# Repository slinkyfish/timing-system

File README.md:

# timing-system
Components for a micromouse and line follower contest timing system.

Initial development will be related to a drag race timer. 

The contest is described here: https://ukmars.org/contests/drag-race/

And the rules are here: https://ukmars.org/contests/contest-rules/drag-race/

The `legacy` folder contains design files for the existing equipment used in UK contests at Birmingham City University and originally designed by Tony Wilcox.

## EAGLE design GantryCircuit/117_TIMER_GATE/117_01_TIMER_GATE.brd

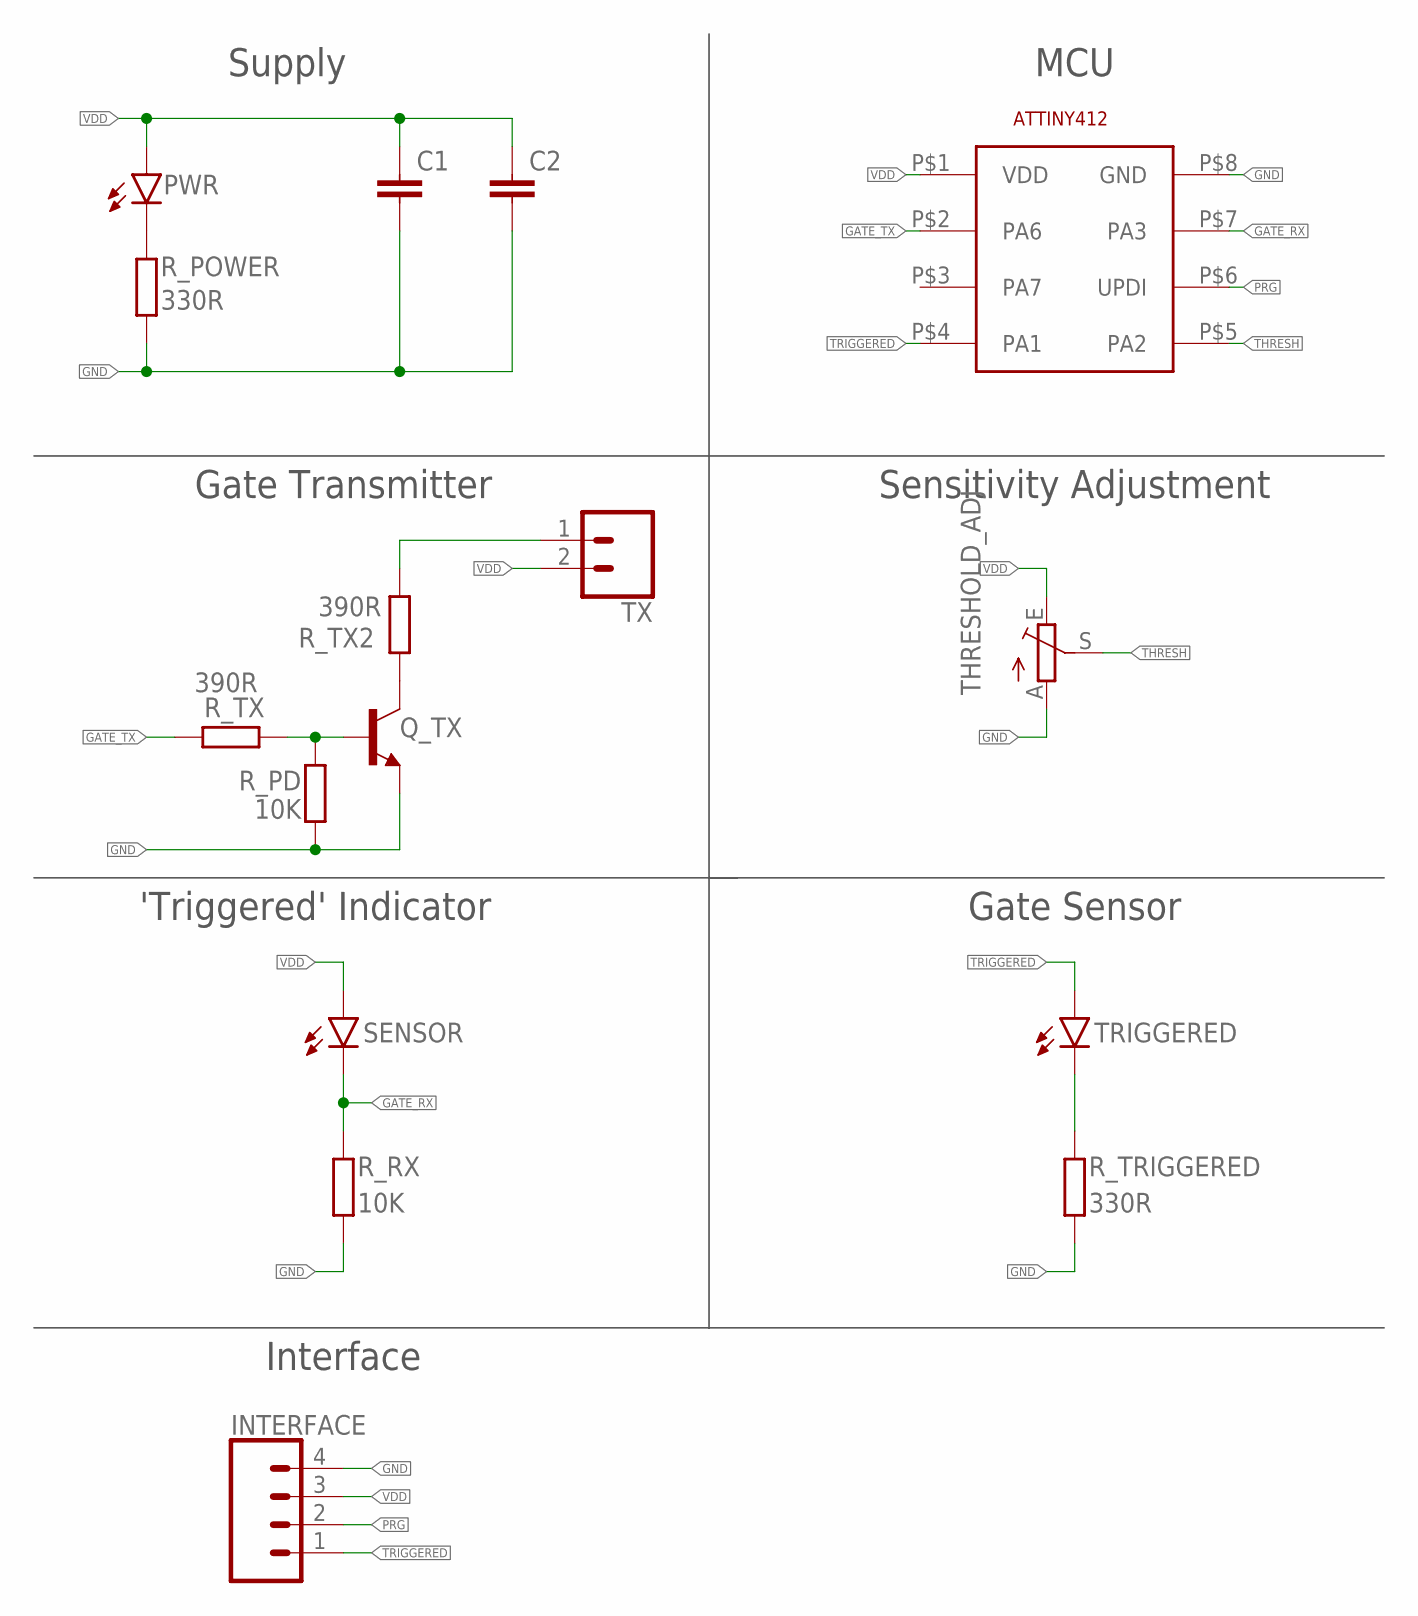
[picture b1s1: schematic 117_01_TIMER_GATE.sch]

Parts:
C1, C2: C-EUC0805K; C0805K
INTERFACE: CONN_04LONGPADS; 1X04_LONGPADS
PWR: LEDSML0805; SML0805
Q_TX: 2N2222-NPN-TO92-EBC; TO92-EBC
R_PD: 10K; M0805
R_POWER: 330R; M0805
R_RX: 10K; M0805
R_TRIGGERED: 330R; M0805
R_TX, R_TX2: 390R; M0805
SENSOR: LED5MM; LED_5MM
THRESHOLD_ADJ: TRIM_EU-S64W; S64W
TRIGGERED: LED5MM; LED_5MM
TX: CONN_02PTH3; 1X02_LONGPADS
U$1: ATTINY412

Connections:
GATE_RX: R_RX.2, SENSOR.K (C), U$1.P$7 (PA3)
GATE_TX: R_TX.2, U$1.P$2 (PA6)
GND: C1.2, C2.2, INTERFACE.4, Q_TX.E, R_PD.2, R_POWER.1, R_RX.1, R_TRIGGERED.1, THRESHOLD_ADJ.A, U$1.P$8 (GND)
unnamed: PWR.C, R_POWER.2
unnamed: R_TX2.1, TX.1
unnamed: Q_TX.B, R_PD.1, R_TX.1
unnamed: Q_TX.C, R_TX2.2
unnamed: R_TRIGGERED.2, TRIGGERED.K (C)
PRG: INTERFACE.2, U$1.P$6 (UPDI)
THRESH: THRESHOLD_ADJ.S, U$1.P$5 (PA2)
TRIGGERED: INTERFACE.1, TRIGGERED.A, U$1.P$4 (PA1)
VDD: C1.1, C2.1, INTERFACE.3, PWR.A, SENSOR.A, THRESHOLD_ADJ.E, TX.2, U$1.P$1 (VDD)

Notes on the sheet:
Gate Sensor
'Triggered' Indicator
Sensitivity Adjustment
Supply
MCU
Gate Transmitter
Interface

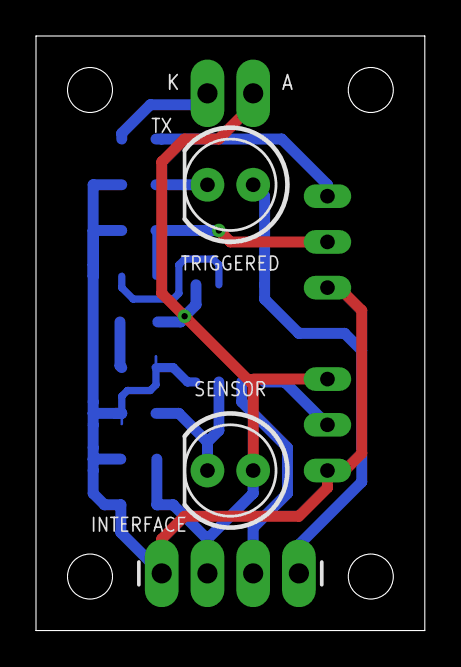
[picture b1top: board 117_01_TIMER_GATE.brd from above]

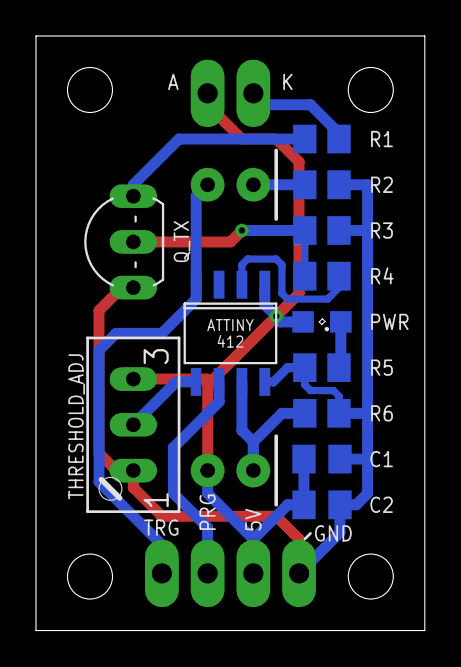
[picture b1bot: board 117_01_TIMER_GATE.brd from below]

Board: 2 copper layers, 21.6 x 33.0 mm, 16 parts (12 on the bottom side), 12 nets.

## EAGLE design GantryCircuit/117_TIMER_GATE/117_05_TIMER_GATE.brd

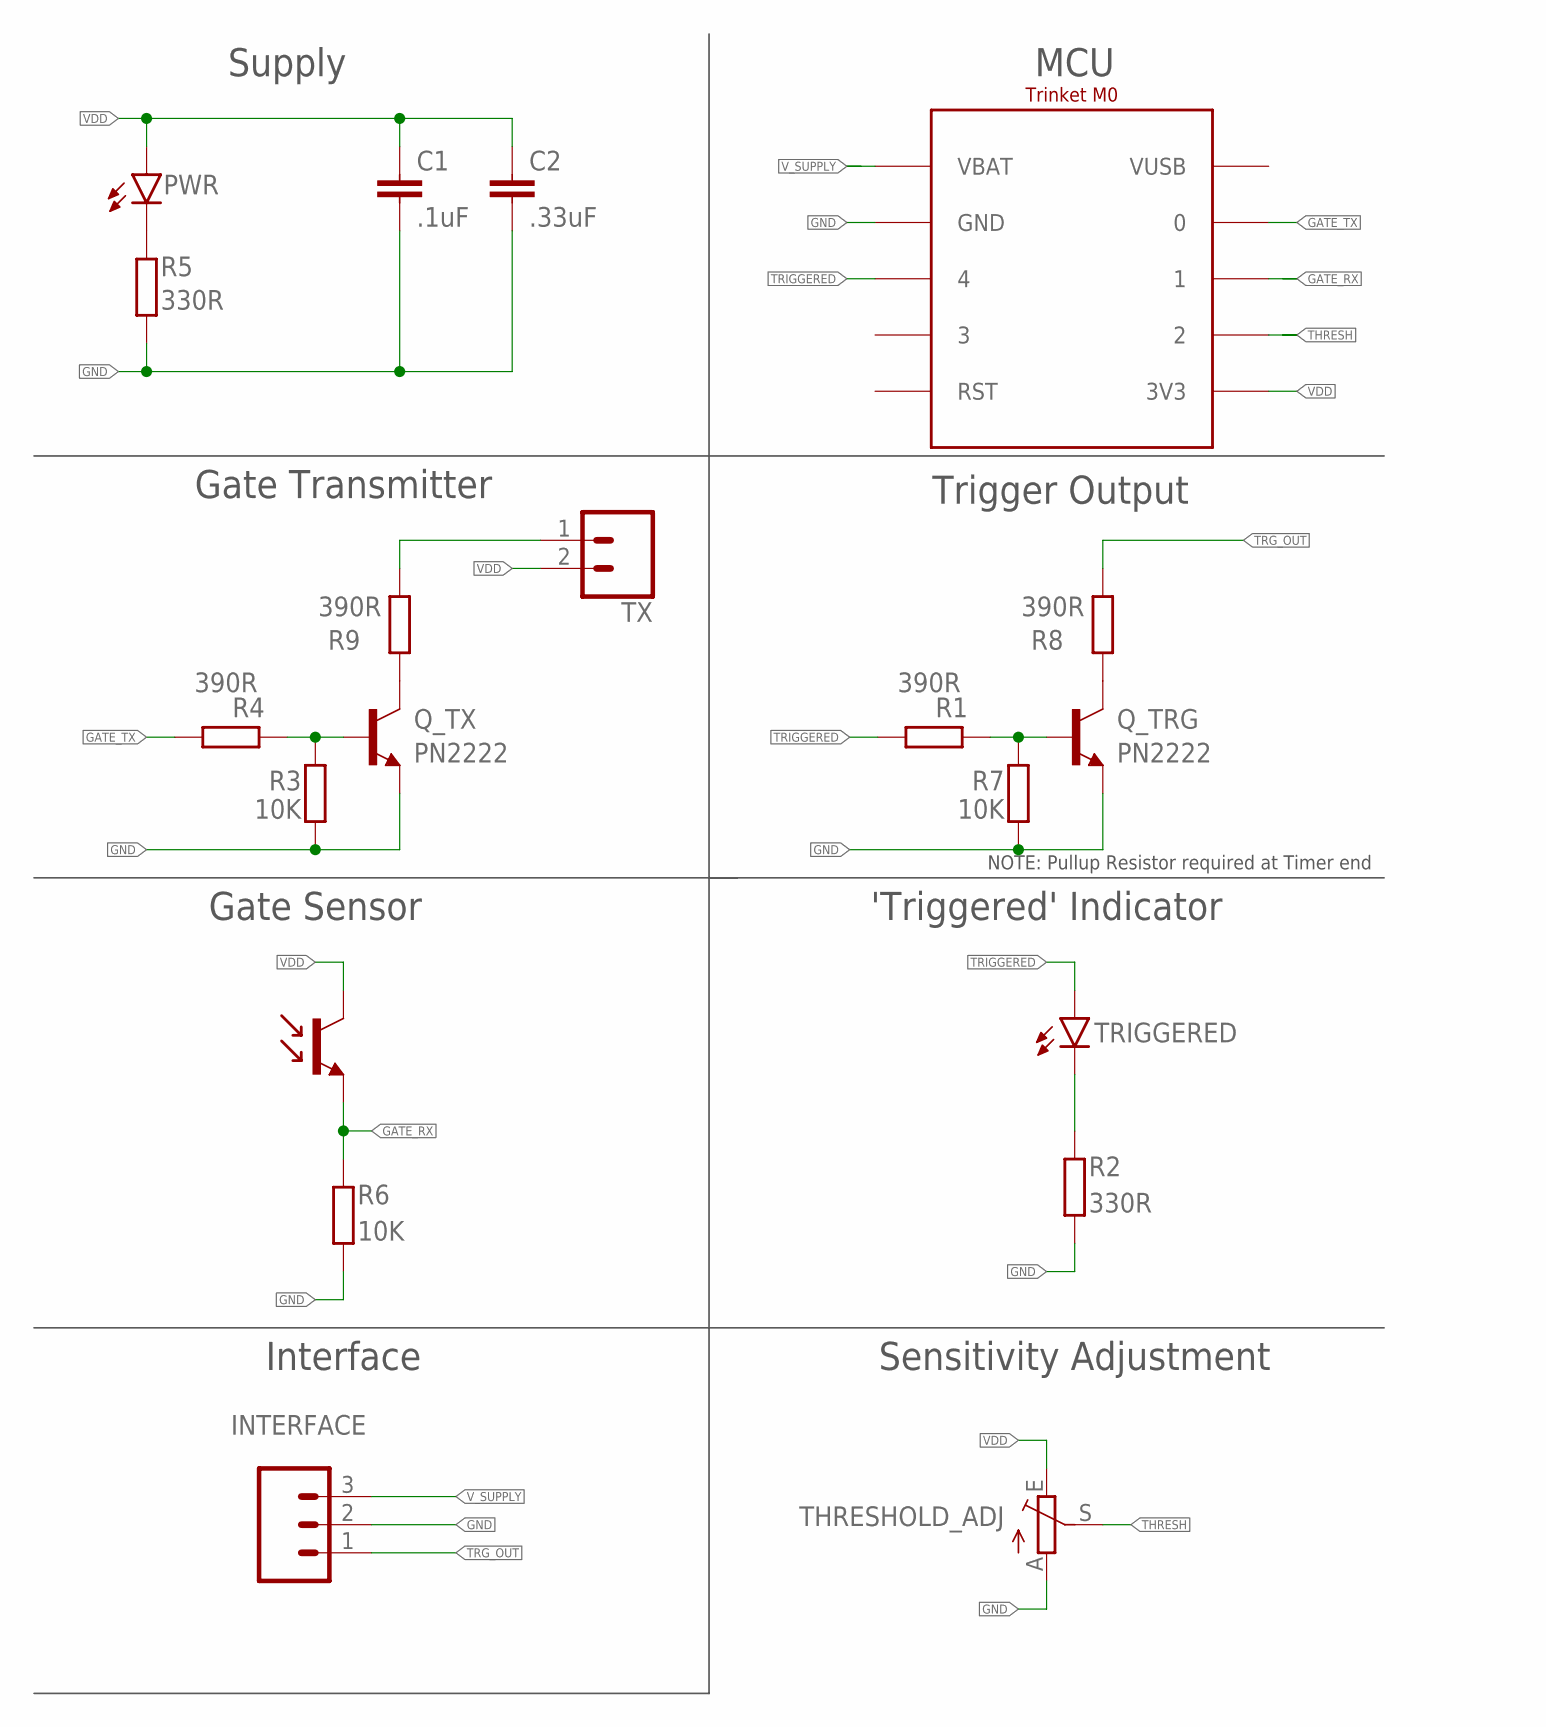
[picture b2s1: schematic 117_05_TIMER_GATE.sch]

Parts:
C1: .1uF; C0805K
C2: .33uF; C0805K
INTERFACE: CONN_03LONGPADS; 1X03_LONGPADS
PWR: LEDSML0805; SML0805
Q_TRG: PN2222; TO92-EBC
Q_TX: PN2222; TO92-EBC
R1, R4, R8, R9: 390R; M0805
R2, R5: 330R; M0805
R3, R6, R7: 10K; M0805
THRESHOLD_ADJ: TRIM_EU-S64W; S64W
TRIGGERED: LED5MM; LED_5MM
TX: CONN_02PTH3; 1X02_LONGPADS
U$1: TRINKETM0
U$2: PHOTOTRANSISTOR; LED_5MM

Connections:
GATE_RX: R6.2, U$1.1, U$2.K (E)
GATE_TX: R4.2, U$1.0
GND: C1.2, C2.2, INTERFACE.2, Q_TRG.E, Q_TX.E, R2.1, R3.2, R5.1, R6.1, R7.2, THRESHOLD_ADJ.A, U$1.GND
unnamed: PWR.C, R5.2
unnamed: R9.1, TX.1
unnamed: Q_TRG.B, R1.1, R7.1
unnamed: Q_TX.B, R3.1, R4.1
unnamed: Q_TX.C, R9.2
unnamed: Q_TRG.C, R8.2
unnamed: R2.2, TRIGGERED.K (C)
THRESH: THRESHOLD_ADJ.S, U$1.2
TRG_OUT: INTERFACE.1, R8.1
TRIGGERED: R1.2, TRIGGERED.A, U$1.4
VDD: C1.1, C2.1, PWR.A, THRESHOLD_ADJ.E, TX.2, U$1.3V3, U$2.A (C)
V_SUPPLY: INTERFACE.3, U$1.VBAT

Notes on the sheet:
Gate Sensor
'Triggered' Indicator
Sensitivity Adjustment
Supply
MCU
Gate Transmitter
Interface
Trigger Output
NOTE: Pullup Resistor required at Timer end

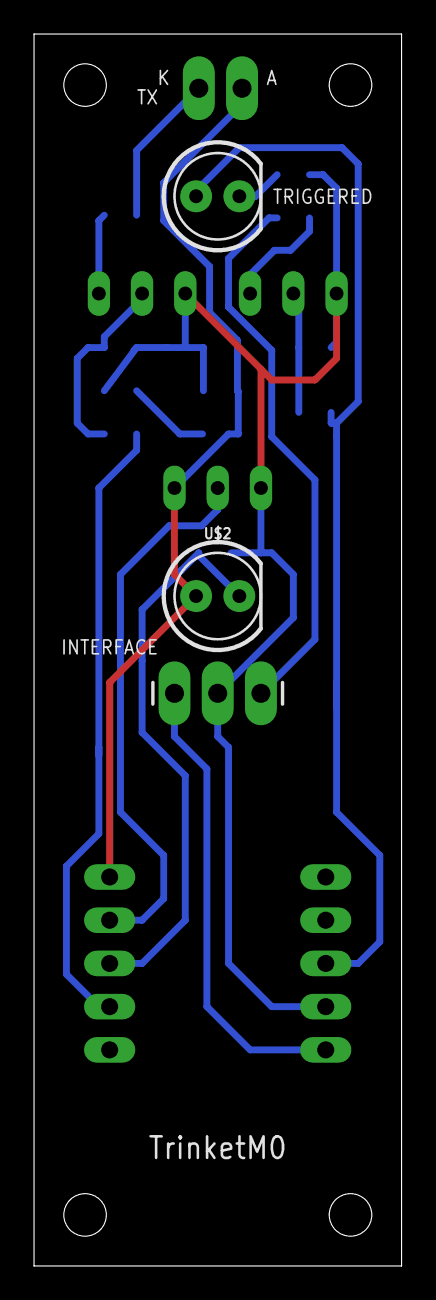
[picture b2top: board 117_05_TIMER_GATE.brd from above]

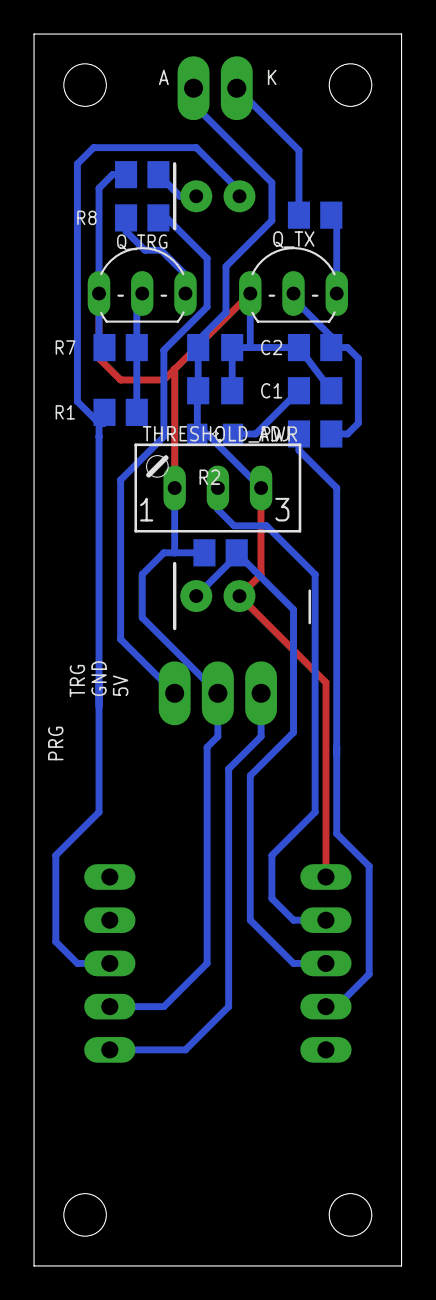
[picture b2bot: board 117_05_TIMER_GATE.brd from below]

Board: 2 copper layers, 21.6 x 72.4 mm, 20 parts (15 on the bottom side), 15 nets.

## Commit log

2021-12-30 add legacy files
2022-01-01 Initial Commit
    Gantry Sch and Brd as they stand
2022-01-01 Block Diagram V1
2022-01-01 added ignore
2022-01-01 added ignore file
2022-01-03 PDF of block diagram

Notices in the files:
parts and their libraries:
SparkFun-Connectors: Licensing: Creative Commons ShareAlike 4.0 International - https://creativecommons.org/licenses/by-sa/4.0
